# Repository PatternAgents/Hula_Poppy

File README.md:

Hula Poppy
=============

PatternAgents Hula Poppy - Pmod Lure for Intel MinnowBoard

[  
*PatternAgents Hula Poppy*](http://www.patternagents.com/projects/Hula_Poppy.html)

PatternAgents Hula Poppy - Pmod Lure for Intel MinnowBoard is a small adaptor board that allows
the Intel MinnowBoard to support Pmod Modules.

This work is licensed under a Creative Commons Attribution-ShareAlike 4.0 International License
[  
*Licensing CC BY-SA 4.0*](http://creativecommons.org/licenses/by-sa/4.0/)

It may be used for Educational, Personal, or Commercial Use, provided you keep these notices,
attribution, and share-alike. When you apply these licenses to material you create, 
it meets the Freedom Defined definition of a "Free Cultural Work". 
Free cultural works are the ones that can be most readily used, shared, 
and remixed by others, and go furthest toward creating a commons of freely reusable materials.

-------------------------------------------------------------------------------------------

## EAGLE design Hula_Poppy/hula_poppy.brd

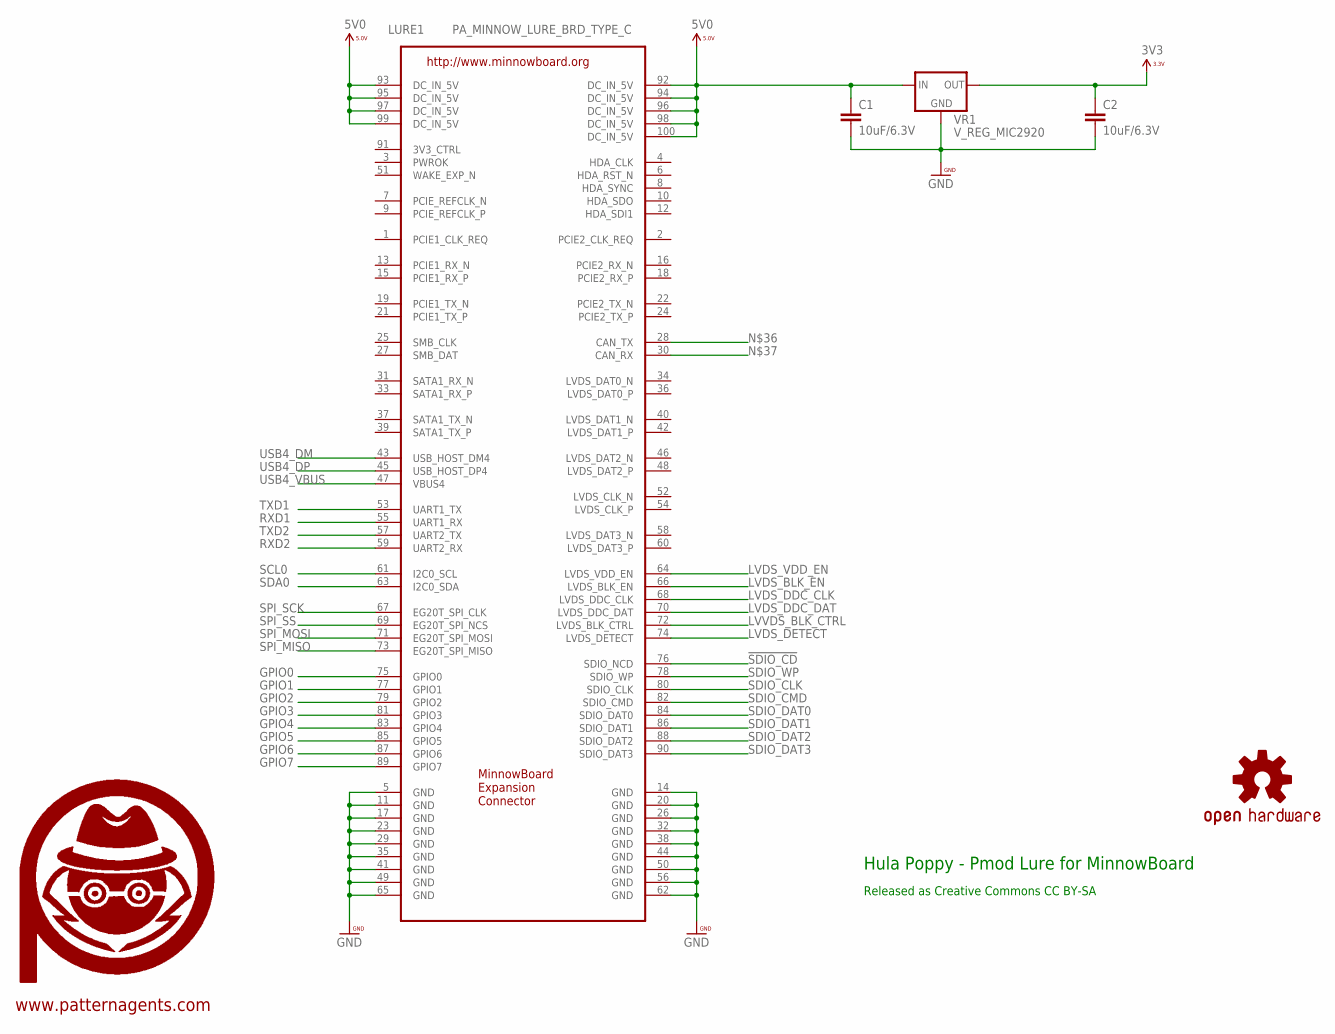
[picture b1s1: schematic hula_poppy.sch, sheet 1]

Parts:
C1, C2: 10uF/6.3V; 0603-CAP
LURE1: PA_MINNOW_LURE_BRD_TYPE_C; PA_LURE_TYPE_C
U$6: PA_LOGO_SYMMED; PA_LOGO_AGENT_MED_SYM
U$8: OSHW_LOGO_SYMWTXT; OSHW_LOGO_TEXT_SYM
VR1: V_REG_MIC2920; SOT223

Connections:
3V3: C2.1, VR1.3 (OUT); also elsewhere on the board
3V3_CTRL: LURE1.91 (3V3_CTRL)
5V0: C1.1, LURE1.92 (DC_IN_5V), LURE1.93 (DC_IN_5V), LURE1.94 (DC_IN_5V), LURE1.95 (DC_IN_5V), LURE1.96 (DC_IN_5V), LURE1.97 (DC_IN_5V), LURE1.98 (DC_IN_5V), LURE1.99 (DC_IN_5V), LURE1.100 (DC_IN_5V), VR1.1 (IN)
!SDIO_CD: LURE1.76 (SDIO_NCD); also elsewhere on the board
GND: C1.2, C2.2, LURE1.5 (GND), LURE1.11 (GND), LURE1.14 (GND), LURE1.17 (GND), LURE1.20 (GND), LURE1.23 (GND), LURE1.26 (GND), LURE1.29 (GND), LURE1.32 (GND), LURE1.35 (GND), LURE1.38 (GND), LURE1.41 (GND), LURE1.44 (GND), LURE1.49 (GND), LURE1.50 (GND), LURE1.56 (GND), LURE1.62 (GND), LURE1.65 (GND), VR1.2 (GND); also elsewhere on the board
GPIO0: LURE1.75 (GPIO0); also elsewhere on the board
GPIO1: LURE1.77 (GPIO1); also elsewhere on the board
GPIO2: LURE1.79 (GPIO2); also elsewhere on the board
GPIO3: LURE1.81 (GPIO3); also elsewhere on the board
GPIO4: LURE1.83 (GPIO4); also elsewhere on the board
GPIO5: LURE1.85 (GPIO5); also elsewhere on the board
GPIO6: LURE1.87 (GPIO6); also elsewhere on the board
GPIO7: LURE1.89 (GPIO7); also elsewhere on the board
LVDS_BLK_EN: LURE1.66 (LVDS_BLK_EN)
LVDS_DDC_CLK: LURE1.68 (LVDS_DDC_CLK)
LVDS_DDC_DAT: LURE1.70 (LVDS_DDC_DAT)
LVDS_DETECT: LURE1.74 (LVDS_DETECT)
LVDS_VDD_EN: LURE1.64 (LVDS_VDD_EN)
LVVDS_BLK_CTRL: LURE1.72 (LVDS_BLK_CTRL)
RXD1: LURE1.55 (UART1_RX); also elsewhere on the board
RXD2: LURE1.59 (UART2_RX); also elsewhere on the board
SCL0: LURE1.61 (I2C0_SCL); also elsewhere on the board
SDA0: LURE1.63 (I2C0_SDA); also elsewhere on the board
SDIO_CLK: LURE1.80 (SDIO_CLK); also elsewhere on the board
SDIO_CMD: LURE1.82 (SDIO_CMD); also elsewhere on the board
SDIO_DAT0: LURE1.84 (SDIO_DAT0); also elsewhere on the board
SDIO_DAT1: LURE1.86 (SDIO_DAT1); also elsewhere on the board
SDIO_DAT2: LURE1.88 (SDIO_DAT2); also elsewhere on the board
SDIO_DAT3: LURE1.90 (SDIO_DAT3); also elsewhere on the board
SDIO_WP: LURE1.78 (SDIO_WP); also elsewhere on the board
SPI_MISO: LURE1.73 (EG20T_SPI_MISO); also elsewhere on the board
SPI_MOSI: LURE1.71 (EG20T_SPI_MOSI); also elsewhere on the board
SPI_SCK: LURE1.67 (EG20T_SPI_CLK); also elsewhere on the board
SPI_SS: LURE1.69 (EG20T_SPI_NCS); also elsewhere on the board
TXD1: LURE1.53 (UART1_TX); also elsewhere on the board
TXD2: LURE1.57 (UART2_TX); also elsewhere on the board
USB4_DM: LURE1.43 (USB_HOST_DM4)
USB4_DP: LURE1.45 (USB_HOST_DP4)
USB4_VBUS: LURE1.47 (VBUS4)

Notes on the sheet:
Hula Poppy - Pmod Lure for MinnowBoard
Released as Creative Commons CC BY-SA
www.patternagents.com

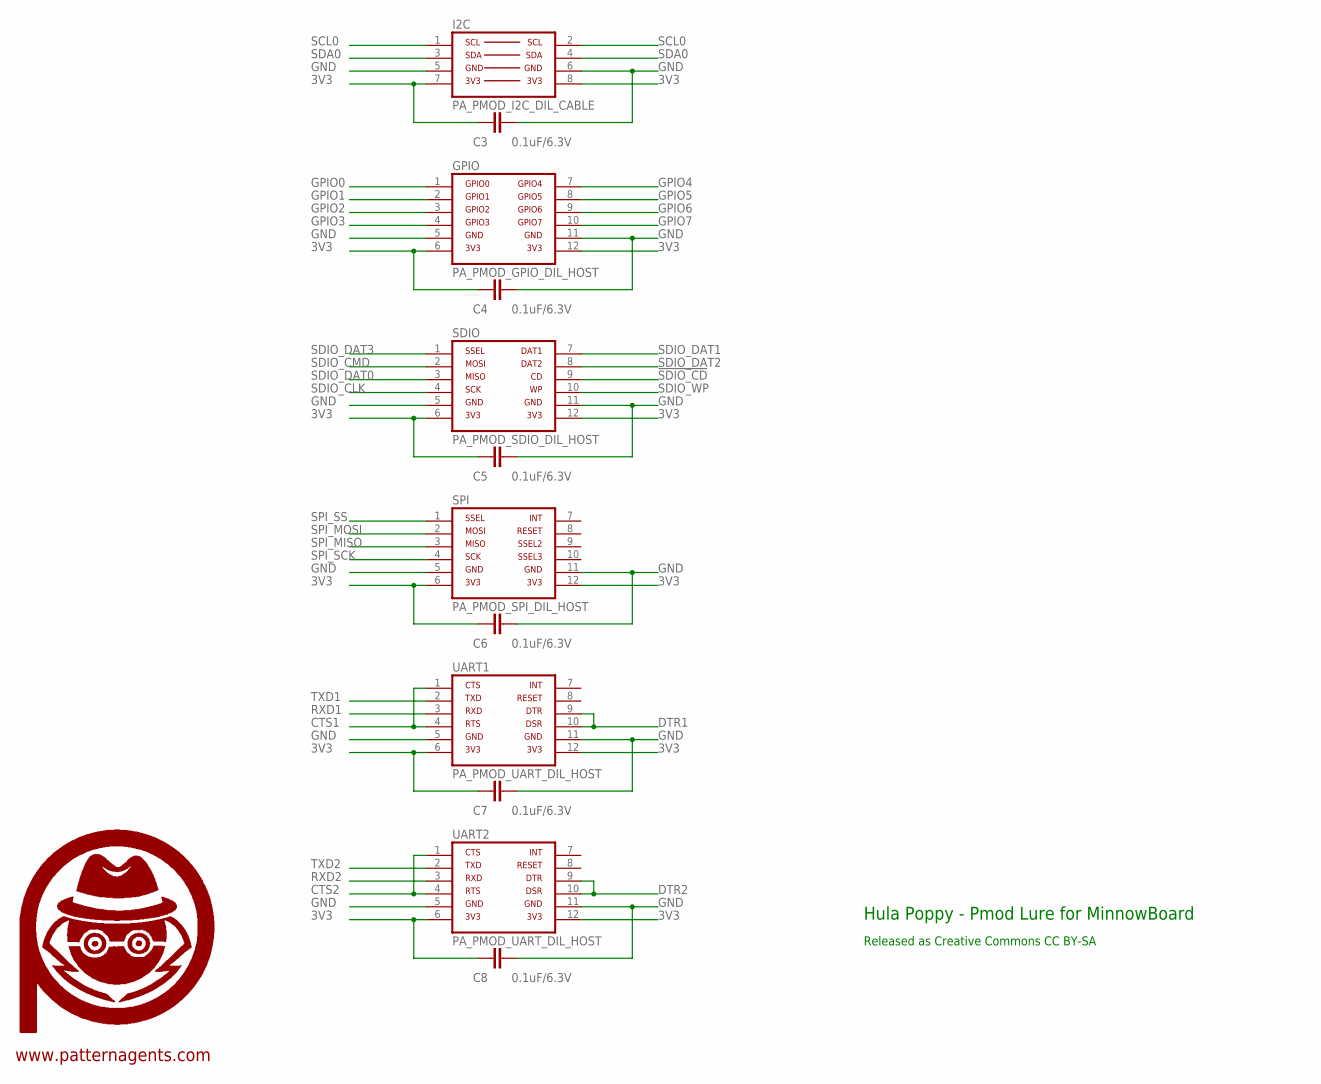
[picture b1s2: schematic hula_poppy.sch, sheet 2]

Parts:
C3, C4, C5, C6, C7, C8: 0.1uF/6.3V; 0603-CAP
GPIO: PA_PMOD_GPIO_DIL_HOST; PA_PMOD_DIL_FEMALE
I2C: PA_PMOD_I2C_DIL_CABLE; PA_PMOD_I2C_CABLE
SDIO: PA_PMOD_SDIO_DIL_HOST; PA_PMOD_DIL_FEMALE
SPI: PA_PMOD_SPI_DIL_HOST; PA_PMOD_DIL_FEMALE
U$10: PA_LOGO_SYMMED; PA_LOGO_AGENT_MED_SYM
UART1, UART2: PA_PMOD_UART_DIL_HOST; PA_PMOD_DIL_FEMALE

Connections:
3V3: C3.2, C4.2, C5.2, C6.2, C7.2, C8.2, GPIO.6, GPIO.12, I2C.7, I2C.8, SDIO.6, SDIO.12, SPI.6, SPI.12, UART1.6, UART1.12, UART2.6, UART2.12; also elsewhere on the board
!SDIO_CD: SDIO.9; also elsewhere on the board
CTS1: UART1.1, UART1.4
CTS2: UART2.1, UART2.4
DTR1: UART1.9, UART1.10
DTR2: UART2.9, UART2.10
GND: C3.1, C4.1, C5.1, C6.1, C7.1, C8.1, GPIO.5, GPIO.11, I2C.5, I2C.6, SDIO.5, SDIO.11, SPI.5, SPI.11, UART1.5, UART1.11, UART2.5, UART2.11; also elsewhere on the board
GPIO0: GPIO.1; also elsewhere on the board
GPIO1: GPIO.2; also elsewhere on the board
GPIO2: GPIO.3; also elsewhere on the board
GPIO3: GPIO.4; also elsewhere on the board
GPIO4: GPIO.7; also elsewhere on the board
GPIO5: GPIO.8; also elsewhere on the board
GPIO6: GPIO.9; also elsewhere on the board
GPIO7: GPIO.10; also elsewhere on the board
RXD1: UART1.3; also elsewhere on the board
RXD2: UART2.3; also elsewhere on the board
SCL0: I2C.1, I2C.2; also elsewhere on the board
SDA0: I2C.3, I2C.4; also elsewhere on the board
SDIO_CLK: SDIO.4; also elsewhere on the board
SDIO_CMD: SDIO.2; also elsewhere on the board
SDIO_DAT0: SDIO.3; also elsewhere on the board
SDIO_DAT1: SDIO.7; also elsewhere on the board
SDIO_DAT2: SDIO.8; also elsewhere on the board
SDIO_DAT3: SDIO.1; also elsewhere on the board
SDIO_WP: SDIO.10; also elsewhere on the board
SPI_MISO: SPI.3; also elsewhere on the board
SPI_MOSI: SPI.2; also elsewhere on the board
SPI_SCK: SPI.4; also elsewhere on the board
SPI_SS: SPI.1; also elsewhere on the board
TXD1: UART1.2; also elsewhere on the board
TXD2: UART2.2; also elsewhere on the board

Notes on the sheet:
Hula Poppy - Pmod Lure for MinnowBoard
Released as Creative Commons CC BY-SA
www.patternagents.com

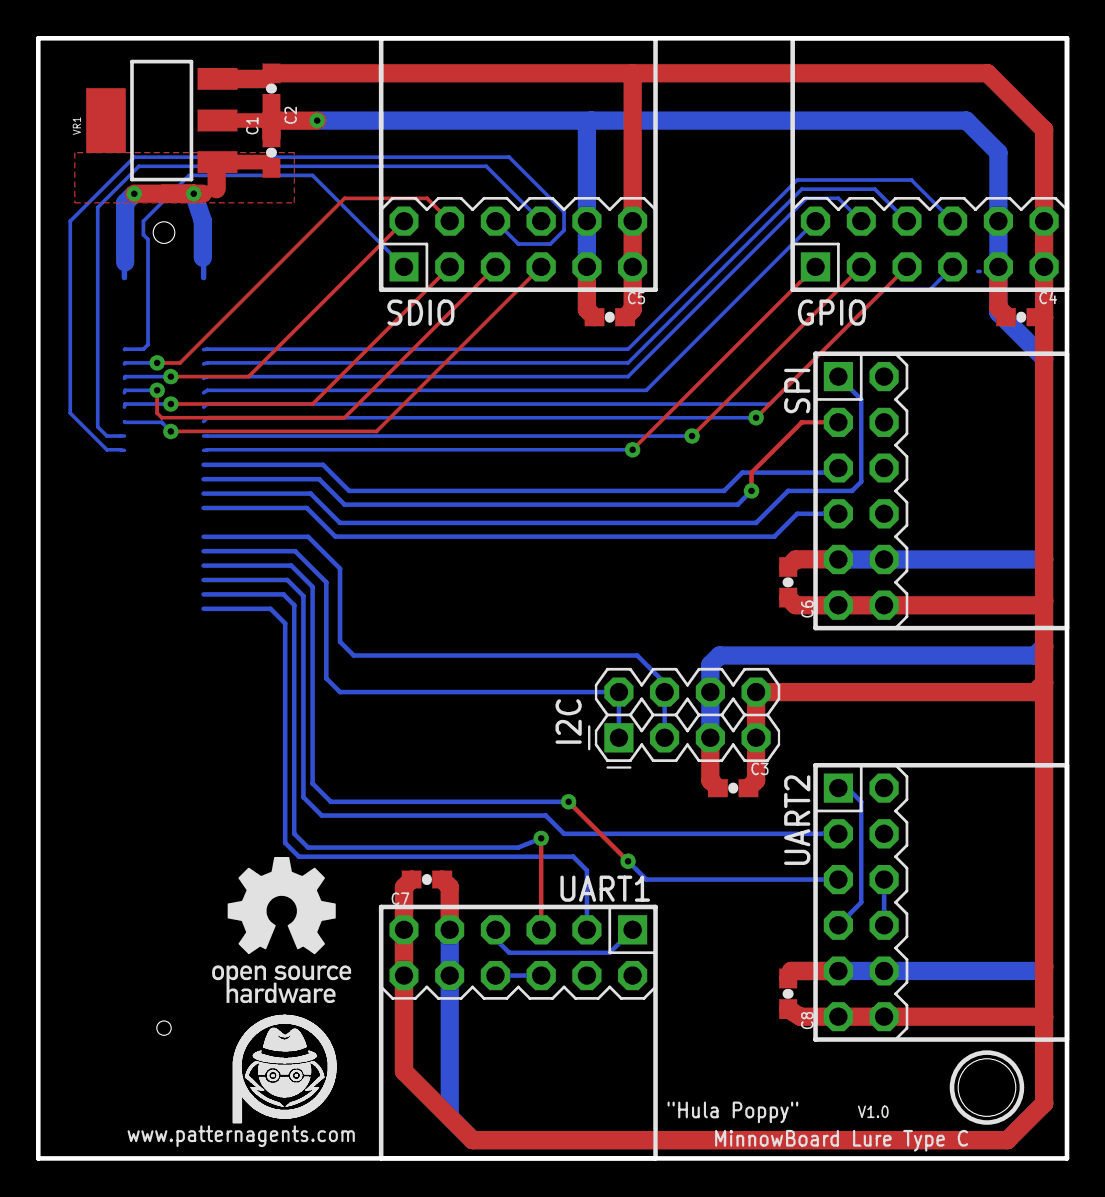
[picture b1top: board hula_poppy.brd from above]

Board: 2 copper layers, 57.1 x 62.2 mm, 20 parts (1 on the bottom side), 33 nets.

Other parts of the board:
U$7: PA_LOGO_SYMMED; PA_LOGO_AGENT_MED_SYM

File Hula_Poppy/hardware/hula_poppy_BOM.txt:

Partlist exported from U:/moxon/My Documents/eagle/PatternAgents/Test_Platforms/Hula_Poppy/hardware/hula_poppy_gerbers/hula_poppy.sch at 12/26/2013 7:46:43 PM

Part  Value                     Device                    Package               Description                                                                    
C1    10uF/6.3V                 CAP0603-CAP               0603-CAP              Capacitor                                                                      
C2    10uF/6.3V                 CAP0603-CAP               0603-CAP              Capacitor                                                                      
C3    0.1uF/6.3V                CAP0603-CAP               0603-CAP              Capacitor                                                                      
C4    0.1uF/6.3V                CAP0603-CAP               0603-CAP              Capacitor                                                                      
C5    0.1uF/6.3V                CAP0603-CAP               0603-CAP              Capacitor                                                                      
C6    0.1uF/6.3V                CAP0603-CAP               0603-CAP              Capacitor                                                                      
C7    0.1uF/6.3V                CAP0603-CAP               0603-CAP              Capacitor                                                                      
C8    0.1uF/6.3V                CAP0603-CAP               0603-CAP              Capacitor                                                                      
GPIO  PA_PMOD_GPIO_DIL_HOST     PA_PMOD_GPIO_DIL_HOST     PA_PMOD_DIL_FEMALE    PatternAgents Peripheral Module GPIO (Type 1A) Pattern                         
I2C   PA_PMOD_I2C_DIL_CABLE     PA_PMOD_I2C_DIL_CABLE     PA_PMOD_I2C_CABLE     PatternAgents Peripheral Module I2C (Standard) Pattern                         
LURE1 PA_MINNOW_LURE_BRD_TYPE_C PA_MINNOW_LURE_BRD_TYPE_C PA_LURE_TYPE_C        PatternAgents Minnow Lure Pattern                                              
SDIO  PA_PMOD_SDIO_DIL_HOST     PA_PMOD_SDIO_DIL_HOST     PA_PMOD_DIL_FEMALE    PatternAgents Peripheral Module SDIO (Type 2B) Pattern                         
SPI   PA_PMOD_SPI_DIL_HOST      PA_PMOD_SPI_DIL_HOST      PA_PMOD_DIL_FEMALE    PatternAgents Peripheral Module SPI (Type 2A) Pattern                          
U$6   PA_LOGO_SYMMED            PA_LOGO_SYMMED            PA_LOGO_AGENT_MED_SYM PatternAgents Logo Symbol                                                      
U$8   OSHW_LOGO_SYMWTXT         OSHW_LOGO_SYMWTXT         OSHW_LOGO_TEXT_SYM    OSHW_LOGO_SYM                                                                  
U$10  PA_LOGO_SYMMED            PA_LOGO_SYMMED            PA_LOGO_AGENT_MED_SYM PatternAgents Logo Symbol                                                      
UART1 PA_PMOD_UART_DIL_HOST     PA_PMOD_UART_DIL_HOST     PA_PMOD_DIL_FEMALE    PatternAgents Peripheral Module UART (Type 4A) Pattern                         
UART2 PA_PMOD_UART_DIL_HOST     PA_PMOD_UART_DIL_HOST     PA_PMOD_DIL_FEMALE    PatternAgents Peripheral Module UART (Type 4A) Pattern                         
VR1   V_REG_MIC2920             V_REG_MIC2920             SOT223                MIC2920A (http://www.micrel.com/_PDF/mic2920.pdf) - 400mA output LDO Regulator

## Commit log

2013-12-27 Version 1.0 Initial Check-In
    Checking-In , Sir?
2013-12-27 Fix Typos in README
2013-12-28 Add more labels to board silkscreen, update gerbers
2013-12-28 Fix README update bug - remove and recheck-in
2013-12-28 Add README
2014-01-05 Correct the project link in index.html

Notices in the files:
parts and their libraries:
PatternAgents-Logos: License : http://creativecommons.org/licenses/by-sa/3.0
(Creative Commons 3.0)
PatternAgents-Boards: License : http://creativecommons.org/licenses/by-sa/4.0
(Creative Commons 4.0)
PatternAgents_Interface: Source License : http://www.digilentinc.com/Pmods/licensing.cfm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
